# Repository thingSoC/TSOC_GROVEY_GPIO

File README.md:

# TSOC_GROVEY_GPIO - thingSoC SX1509 GPIO Module :

[TSOC_GROVEY_GPIO](https://github.com/thingSoC/TSOC_GROVEY_GPIO)

---------------------------------------

## TSOC_GROVEY_GPIO Status <a name="TSOC_GROVEY_GPIO_status"/>

**11/06/2016:** 
Revision 1.0 - Initial Layout released to OSHpark

---------------------------------------
## TSOC_GROVEY_GPIO Model Images

[TSOC_GROVEY_GPIO](https://github.com/thingSoC/TSOC_GROVEY_GPIO)

[TSOC_GROVEY_GPIO](https://github.com/thingSoC/TSOC_GROVEY_GPIO)

---------------------------------------

## TSOC_GROVEY_GPIO Documentation Index <a name="TSOC_GROVEY_GPIO_documentation_index"/>

[TSOC_GROVEY_GPIO Project](http://thingsoc.github.io/projects/TSOC_GROVEY_GPIO.html)

[TSOC_GROVEY_GPIO Hardware](https://github.com/thingSoC/TSOC_GROVEY_GPIO/tree/master/TSOC_GROVEY_GPIO/hardware)

---------------------------------------

## thingSoC Documentation Index <a name="thingSoC_documentation_index"/>

[thingSoC Organization Website](http://thingSoC.github.io)

[thingSoC FAQ - Frequently Asked Questions](http://thingsoc.github.io/support/faq.html)

---------------------------------------

[ 
*thingSoC*](http://thingsoc.github.io)

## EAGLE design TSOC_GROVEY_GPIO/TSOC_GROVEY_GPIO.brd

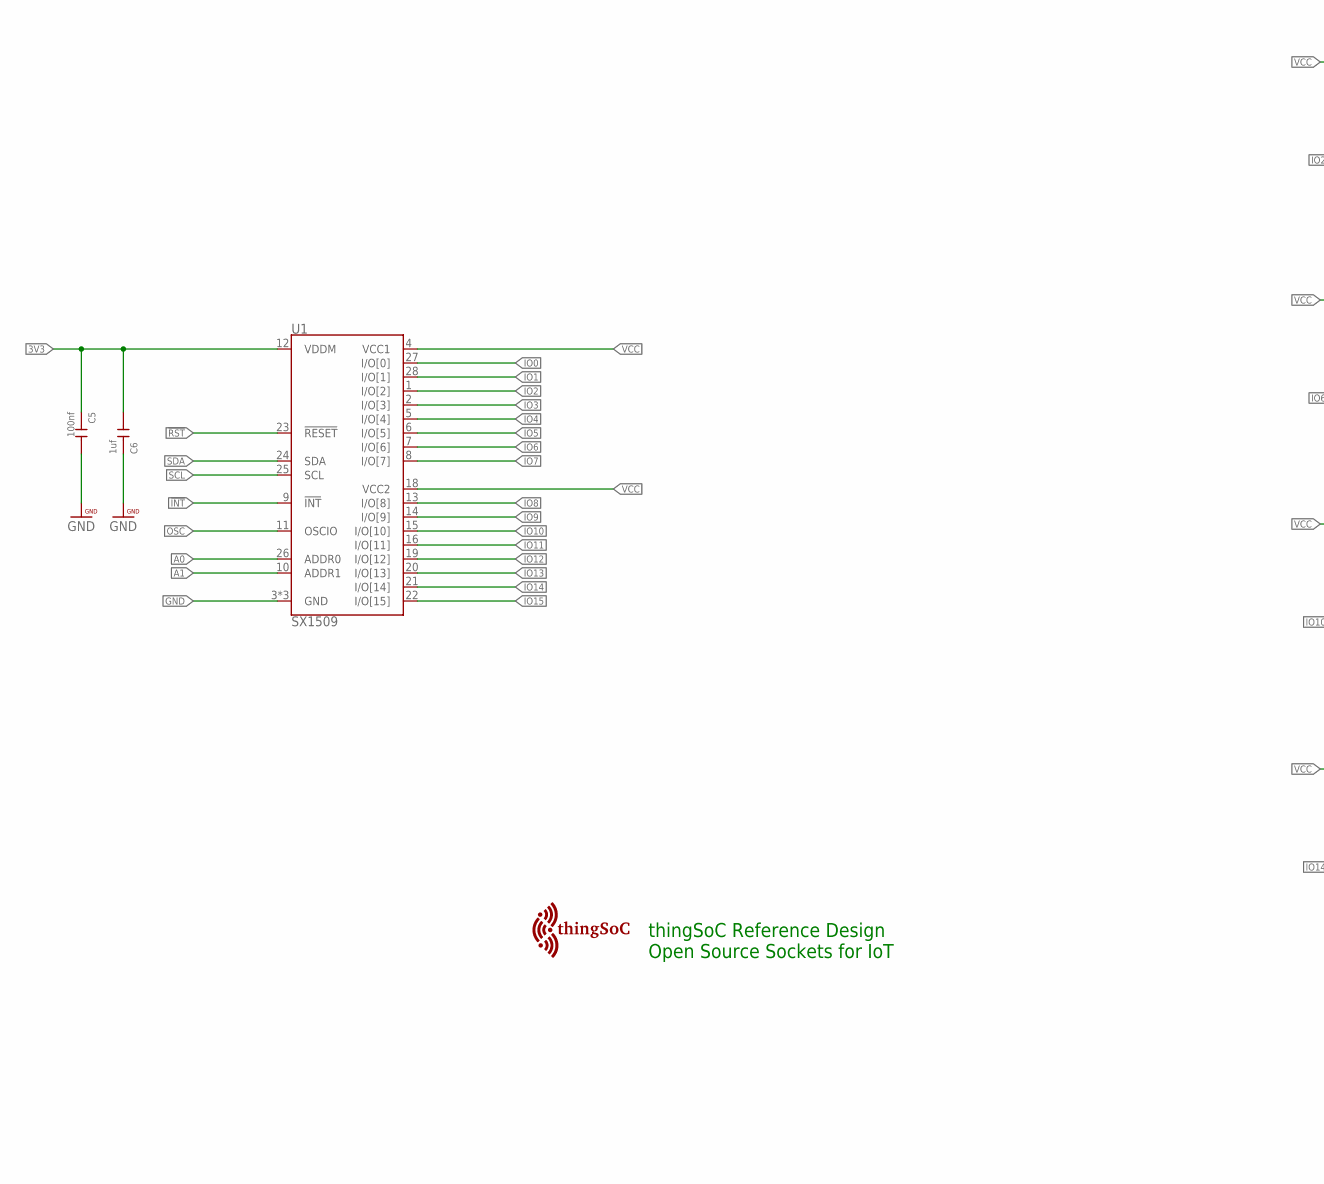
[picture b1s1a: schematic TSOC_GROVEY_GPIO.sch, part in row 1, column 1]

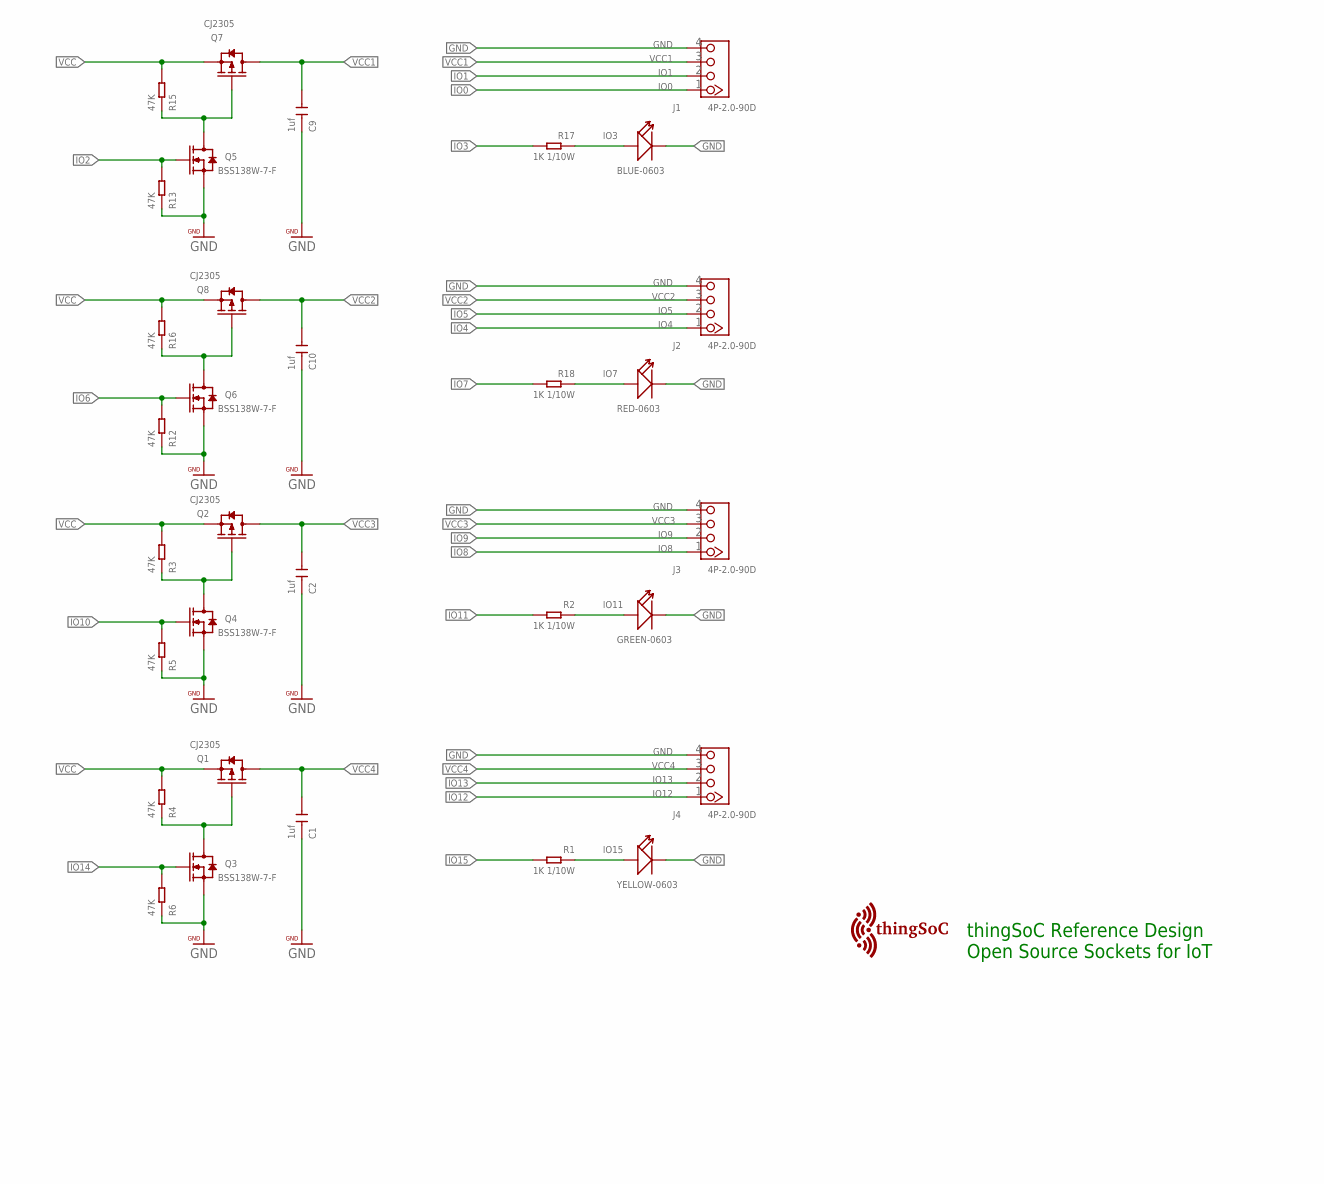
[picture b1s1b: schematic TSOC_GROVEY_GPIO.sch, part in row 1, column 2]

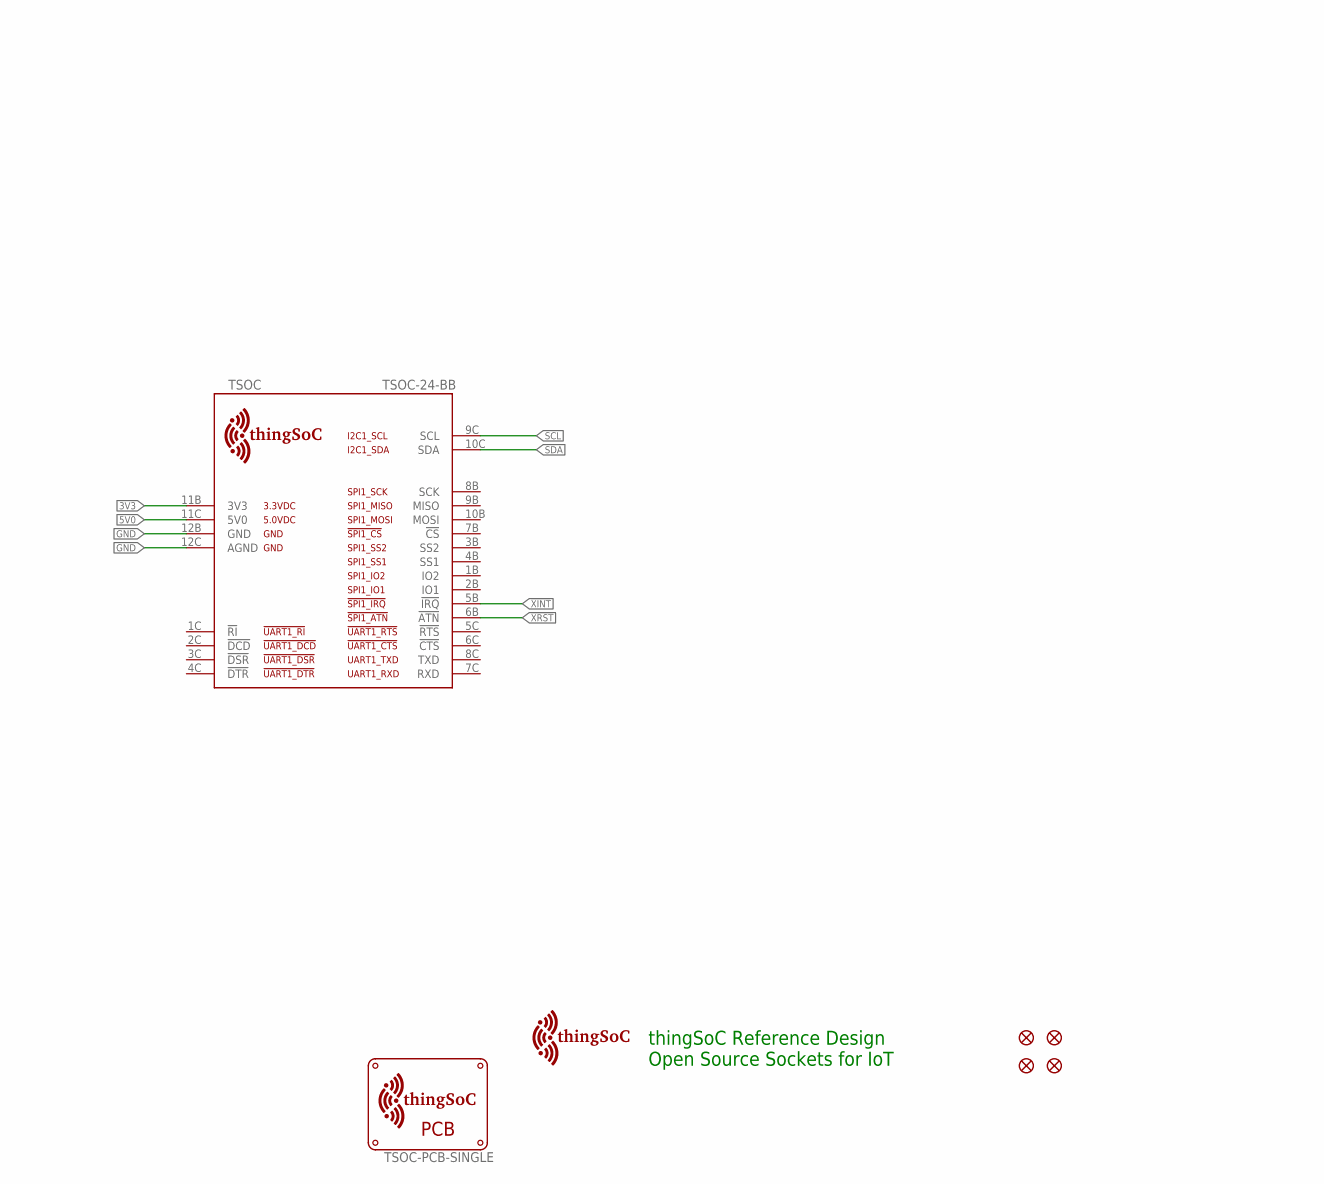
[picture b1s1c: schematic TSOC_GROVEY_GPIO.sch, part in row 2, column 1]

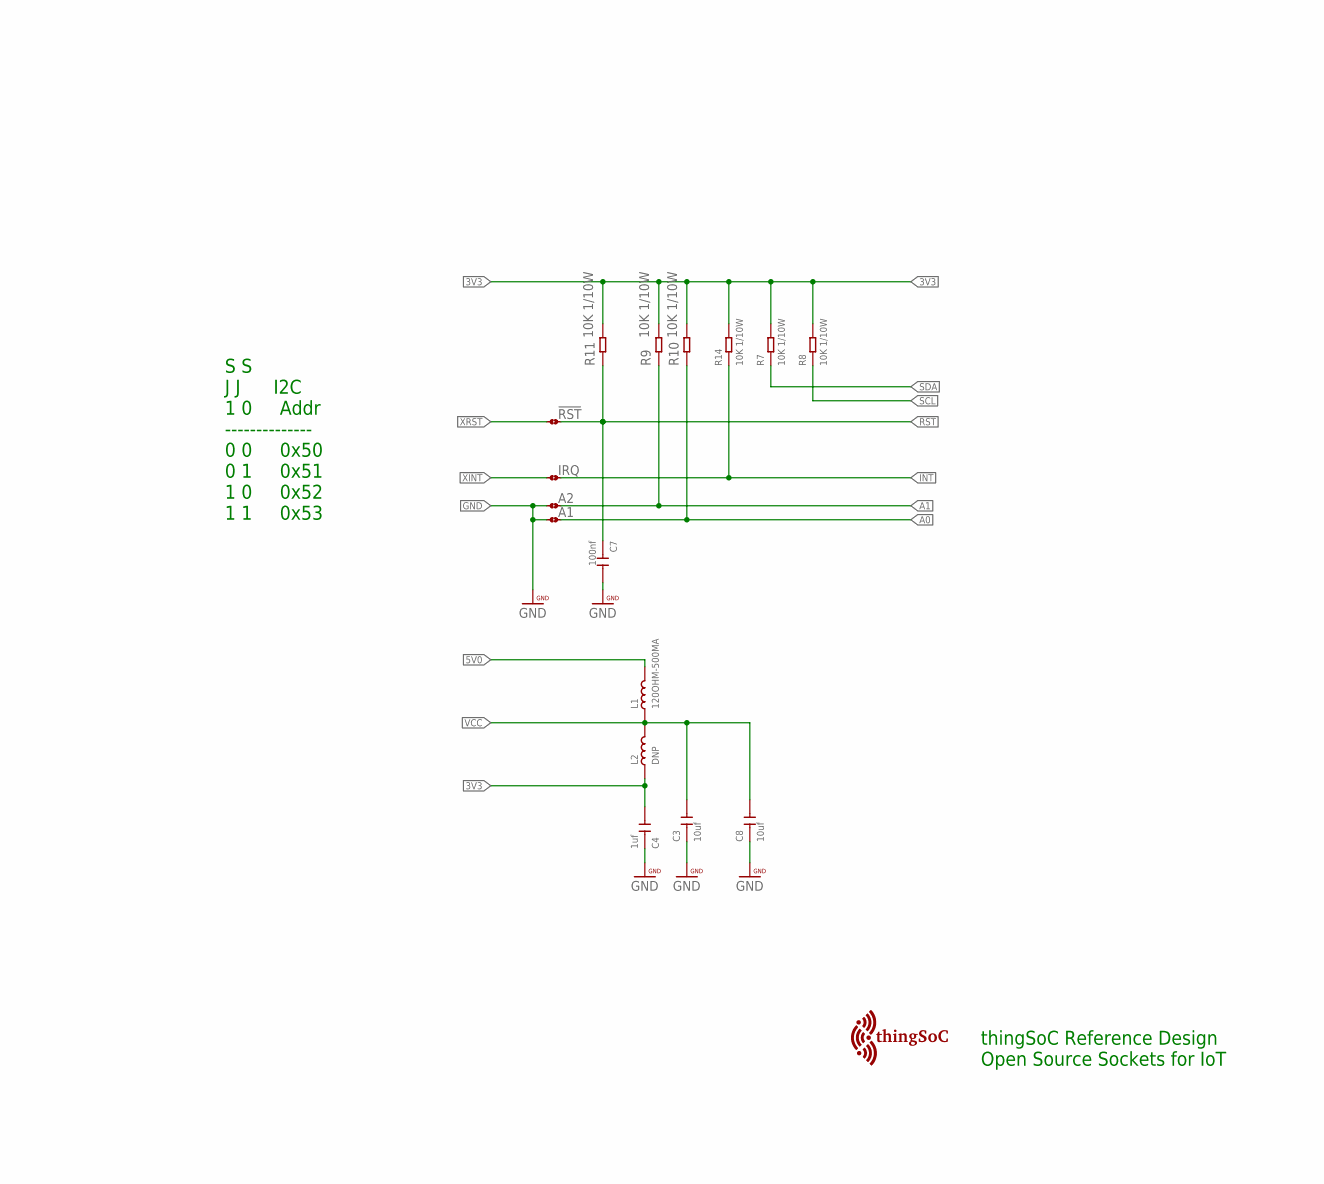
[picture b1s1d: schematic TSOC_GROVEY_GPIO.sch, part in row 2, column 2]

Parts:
!RST: NO; JMP-2-NO
$$U$1, $$U$2: TSOC-LOGO-SMALL; TSOC-LOGO-SML
A1, A2: NO; JMP-2-NO
C1, C2, C4, C6, C9, C10: 1uf; C0603
C3, C8: 10uf; C1206
C5, C7: 100nf; C0603
FID1, FID2, FID3, FID4: FIDUCIALUFIDUCIAL; MICRO-FIDUCIAL
IO3: BLUE-0603; LED-0603
IO7: RED-0603; LED-0603
IO11: GREEN-0603; LED-0603
IO15: YELLOW-0603; LED-0603
IRQ: NO; JMP-2-NO
J1, J2, J3, J4: 4P-2.0-90D; HW4-2.0-90D
L1: 120OHM-500MA; L0603
L2: DNP; L0603
Q1, Q2, Q7, Q8: CJ2305; SOT-23
Q3, Q4, Q5, Q6: BSS138W-7-F; SOT-23
R1, R2, R17, R18: 1K 1/10W; R0603
R3, R4, R5, R6, R12, R13, R15, R16: 47K; R0603
R7, R8, R9, R10, R11, R14: 10K 1/10W; R0603
TSOC: TSOC-24-BB; TSOC-BB-S24
U1: SX1509; QFN-28
U$3: TSOC-PCB-SINGLE; TSOC-BB-BRD-DIM
U$101: TSOC-LOGO-LRG
U$102: TSOC-LOGO-SMALL; TSOC-LOGO-SML

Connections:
3V3: C4.2, C5.1, C6.2, L2.1, R7.2, R8.2, R9.2, R10.2, R11.2, R14.2, TSOC.11B (3V3), U1.12 (VDDM)
5V0: L1.2, TSOC.11C (5V0)
!INT: IRQ.2, R14.1, U1.9 (!INT)
!RST: !RST.1, C7.1, R11.1, U1.23 (!RESET)
!XINT: IRQ.1, TSOC.5B (!IRQ)
!XRST: !RST.2, TSOC.6B (!ATN)
A0: A1.2, R10.1, U1.26 (ADDR0)
A1: A2.2, R9.1, U1.10 (ADDR1)
GND: A1.1, A2.1, C1.1, C2.1, C3.1, C4.1, C5.2, C6.1, C7.2, C8.1, C9.1, C10.1, IO3.-, IO7.-, IO11.-, IO15.-, J1.4, J2.4, J3.4, J4.4, Q3.2 (S), Q4.2 (S), Q5.2 (S), Q6.2 (S), R5.1, R6.1, R12.1, R13.1, TSOC.12B (GND), TSOC.12C (AGND), U1.3 (GND), U1.17 (GND), U1.29 (GND)
IO0: J1.1, U1.27 (I/O[0])
IO1: J1.2, U1.28 (I/O[1])
IO2: Q5.1 (G), R13.2, U1.1 (I/O[2])
IO3: R17.2, U1.2 (I/O[3])
IO4: J2.1, U1.5 (I/O[4])
IO5: J2.2, U1.6 (I/O[5])
IO6: Q6.1 (G), R12.2, U1.7 (I/O[6])
IO7: R18.2, U1.8 (I/O[7])
IO8: J3.1, U1.13 (I/O[8])
IO9: J3.2, U1.14 (I/O[9])
IO10: Q4.1 (G), R5.2, U1.15 (I/O[10])
IO11: R2.2, U1.16 (I/O[11])
IO12: J4.1, U1.19 (I/O[12])
IO13: J4.2, U1.20 (I/O[13])
IO14: Q3.1 (G), R6.2, U1.21 (I/O[14])
IO15: R1.2, U1.22 (I/O[15])
LED1: IO11.+, R2.1
LED2: IO7.+, R18.1
LED3: IO3.+, R17.1
LED4: IO15.+, R1.1
unnamed: Q2.1 (G), Q4.3 (D), R3.1
unnamed: Q1.1 (G), Q3.3 (D), R4.1
unnamed: Q5.3 (D), Q7.1 (G), R15.1
unnamed: Q6.3 (D), Q8.1 (G), R16.1
OSC: U1.11 (OSCIO)
SCL: R8.1, TSOC.9C (SCL), U1.25 (SCL)
SDA: R7.1, TSOC.10C (SDA), U1.24 (SDA)
VCC: C3.2, C8.2, L1.1, L2.2, Q1.2 (S), Q2.2 (S), Q7.2 (S), Q8.2 (S), R3.2, R4.2, R15.2, R16.2, U1.4 (VCC1), U1.18 (VCC2)
VCC1: C9.2, J1.3, Q7.3 (D)
VCC2: C10.2, J2.3, Q8.3 (D)
VCC3: C2.2, J3.3, Q2.3 (D)
VCC4: C1.2, J4.3, Q1.3 (D)

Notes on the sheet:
S S J J I2C 1 0 Addr -------------- 0 0 0x50 0 1 0x51 1 0 0x52 1 1 0x53
thingSoC Reference Design Open Source Sockets for IoT

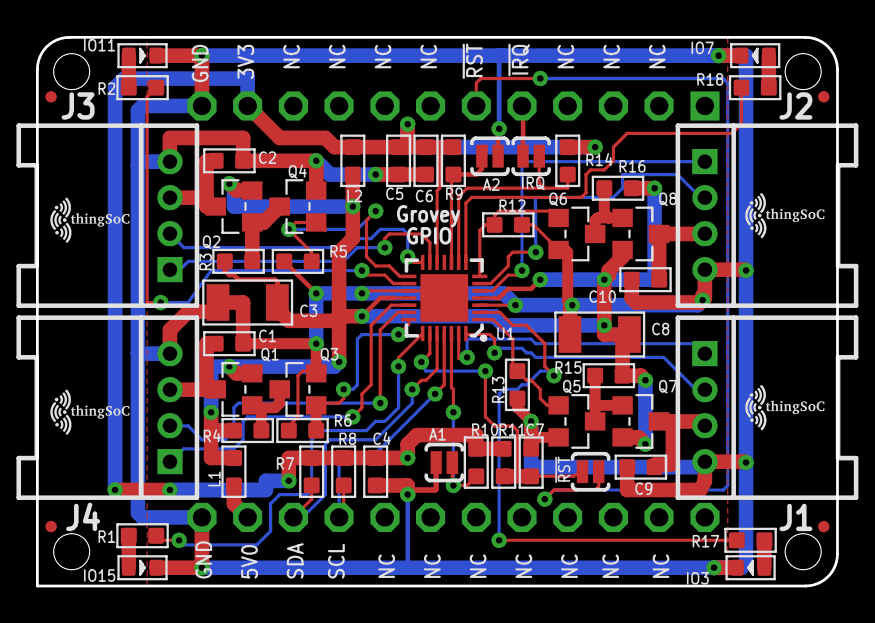
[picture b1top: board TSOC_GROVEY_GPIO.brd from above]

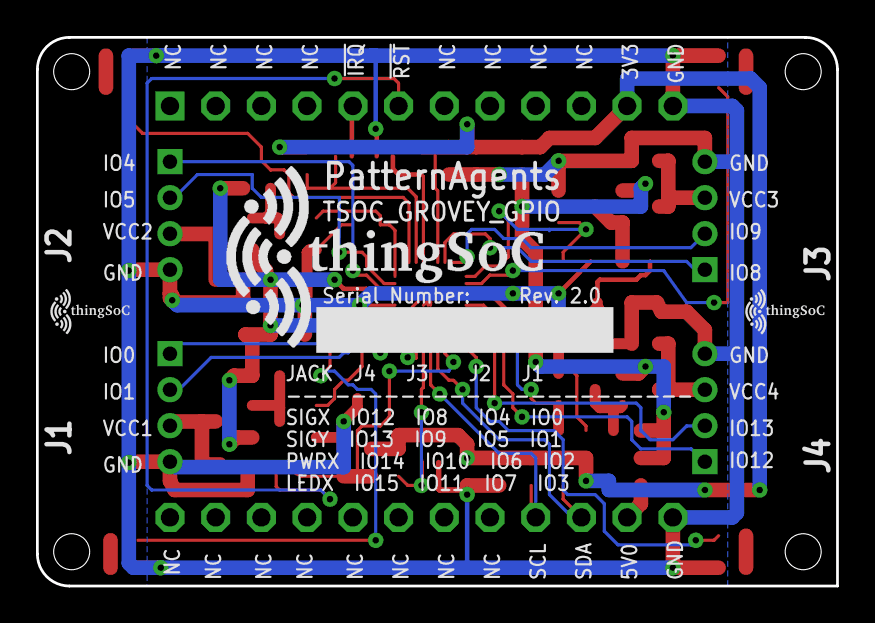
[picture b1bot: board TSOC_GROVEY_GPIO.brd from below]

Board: 2 copper layers, 44.5 x 30.5 mm, 64 parts (3 on the bottom side), 40 nets.

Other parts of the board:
U$1, U$2, U$100: TSOC-LOGO-SMALL; TSOC-LOGO-SML

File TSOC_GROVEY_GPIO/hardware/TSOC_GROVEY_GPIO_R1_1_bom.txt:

Partlist exported from U:/PatternAgents/eagle/TSOC_Modules/TSOC_GROVEY_IO/TSOC_GROVEY_GPIO/hardware/TSOC_GROVEY_GPIO.sch at 1/4/2017 10:25:06 AM

Qty Value             Device                                        Package         Parts                   Description                         
2   100nf             CERAMIC-100NF-50V-10%-X7R(0603)               C0603           C5, C7                  302010138                           
2   100uf             CERAMIC-100UF-6.3V-20%-X5R(1206)              C1206           C3, C9                  302010183                           
6   10K 1/10W         SMD-RES-10K-5%-1/10W(0603)                    R0603           R5, R6, R7, R8, R9, R10 301010293                           
1   120OHM-500MA      SMD-FERRITE-CHIP-120-OHM-500MA(0603)          L0603           L1                      303030001                           
4   1K 1/10W          SMD-RES-1K-5%-1/10W(0603)                     R0603           R1, R2, R13, R14        301010291                           
6   1uf               CERAMIC-1UF-25V-10%-X7R(0603)                 C0603           C1, C2, C4, C6, C8, C10 302010139                           
4   47K               SMD-RES-47K-5%-1/10W(0603)                    R0603           R3, R4, R11, R12        301010084                           
4   4P-2.0-90D        GROVE-CONNECTOR-DIP-90D(4P-2.0)               HW4-2.0-90D     J1, J2, J3, J4          320110034                           
1   BLUE-0603         SMD-LED-CLEAR-BLUE(0603)                      LED-0603        IO3                     304090045                           
4   BSS138W-7-F       SMD-MOSFET-N-CH-50V-200MA-BSS138W-7-F(SOT-23) SOT-23          Q3, Q4, Q5, Q6          305030000                           
4   CJ2305            SMD-MOSFET-P-CH-8V-4.1A-CJ2305(SOT-23)        SOT-23          Q1, Q2, Q7, Q8          305030014                           
1   DNP               SMD-FERRITE-CHIP-120-OHM-500MA(0603)          L0603           L2                      303030001                           
4   FIDUCIALUFIDUCIAL FIDUCIALUFIDUCIAL                             MICRO-FIDUCIAL  FID1, FID2, FID3, FID4  Fiducial Alignment Points           
1   GREEN-0603        SMD-LED-CLEAR-GREEN(0603)                     LED-0603        IO11                    304090043                           
4   NO                JMP-2-NO                                      JMP-2-NO        !RST, A0, A1, IRQ       Basic Jumper - Normally Open        
1   RED-0603          LED-SMD-RED-DIFFUSED(0603)                    LED-0603        IO7                     304090042                           
1   SX1509            SX1509                                        QFN-28          U1                      Semtech SX1509                      
1   TSOC-24-BB        TSOC-24-BB                                    TSOC-BB-S24     TSOC                    thingSoC Twenty-Four(24) Pin Socket 
1   TSOC-LOGO-LRG     TSOC-LOGO-LRG                                 TSOC-LOGO-LRG   U$101                   thingSoC Logo                       
3   TSOC-LOGO-SMALL   TSOC-LOGO-SMALL                               TSOC-LOGO-SML   $$U$4, $$U$5, U$102     thingSoC Logo                       
1   TSOC-PCB-SINGLE   TSOC-PCB-SINGLE                               TSOC-BB-BRD-DIM U$3                     thingSoC PCB Outlines               
1   YELLOW-0603       SMD-LED-CLEAR-YELLOW(0603)                    LED-0603        IO15                    304090044

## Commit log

2017-01-10 update documentation
2017-01-25 update silkscreen
2017-03-01 update docs

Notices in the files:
parts and their libraries:
thingSoC: License : http://creativecommons.org/licenses/by-sa/4.0
(Creative Commons 4.0)
SparkFun-DigitalIC: Licensing: Creative Commons ShareAlike 4.0 International - https://creativecommons.org/licenses/by-sa/4.0
PatternAgents-Beautify: License : http://creativecommons.org/licenses/by-sa/3.0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
